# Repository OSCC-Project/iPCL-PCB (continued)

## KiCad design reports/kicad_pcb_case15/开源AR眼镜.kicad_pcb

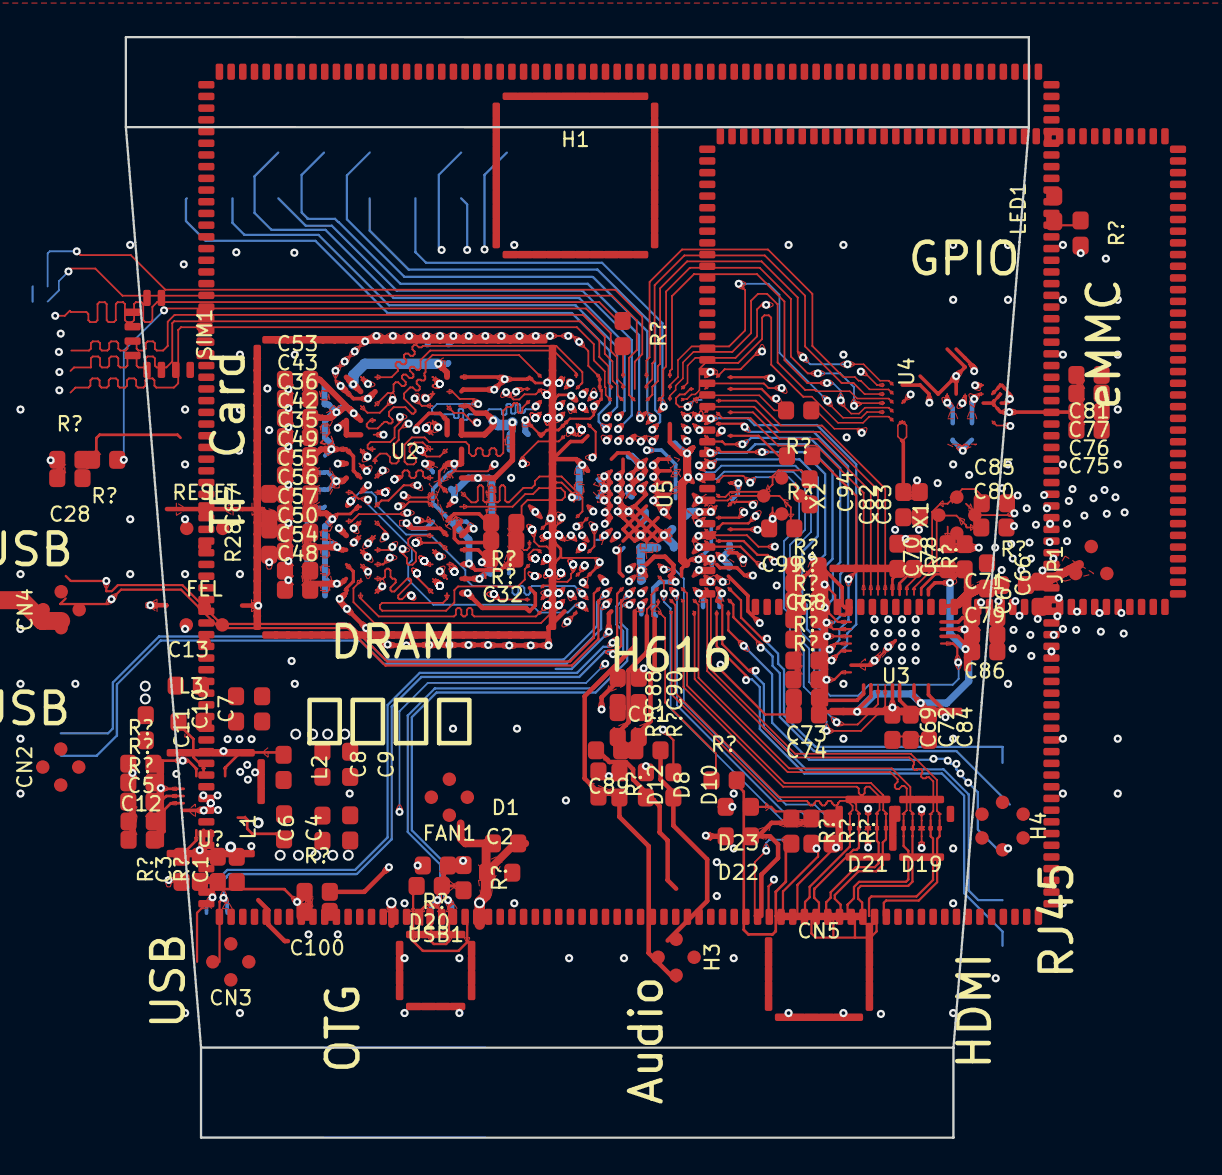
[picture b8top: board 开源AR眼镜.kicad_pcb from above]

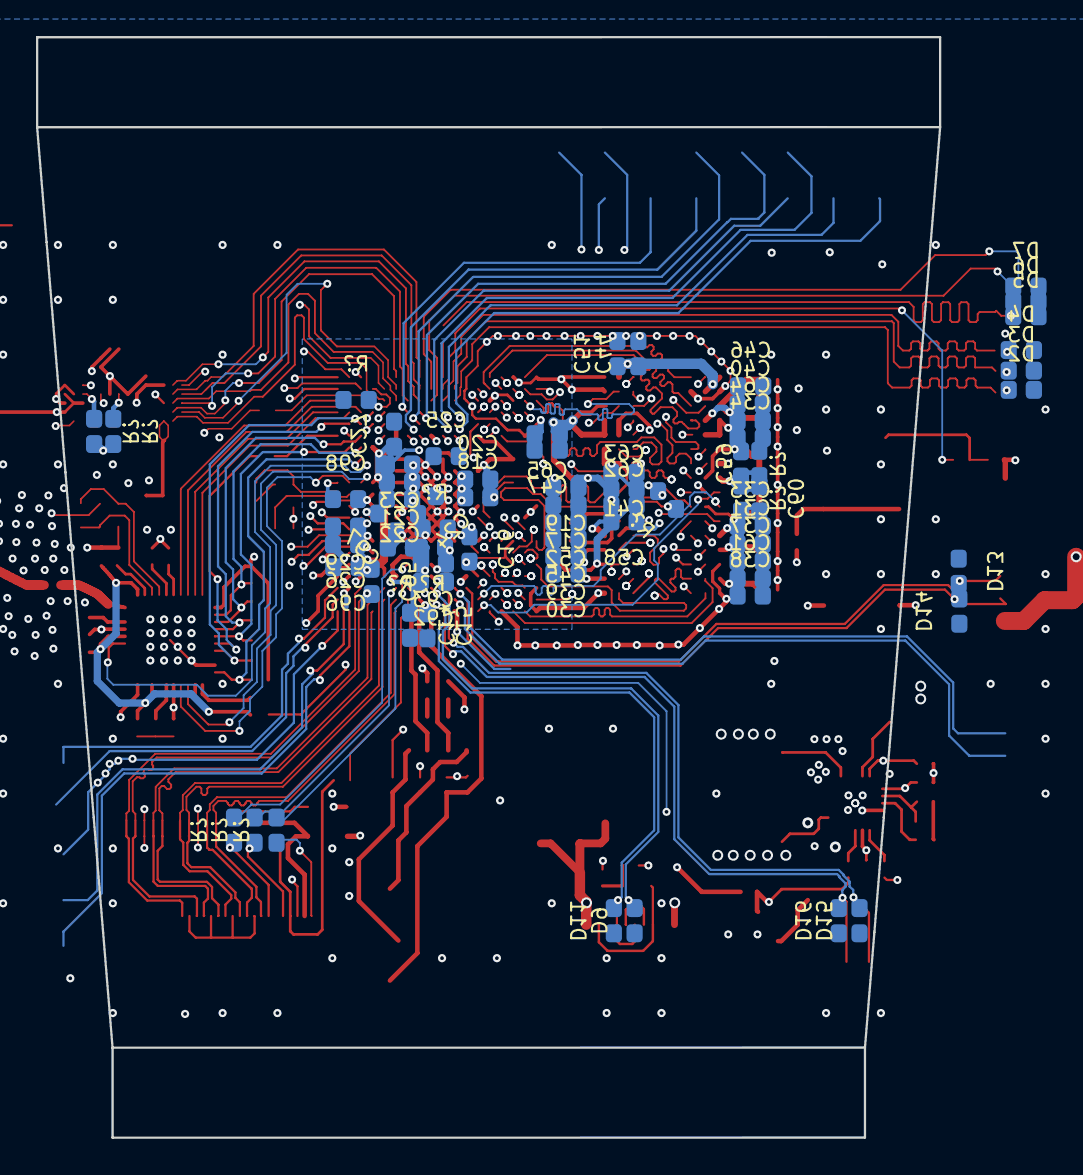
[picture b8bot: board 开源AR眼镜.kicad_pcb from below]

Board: 4 copper layers, 50.2 x 61.1 mm, 190 parts (68 on the bottom side), 205 nets.

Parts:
C1, C3, C5, C14, C15, C16, C17, C18, C19, C20, C21, C22, C23, C24, C25, C26, C27, C29, C30, C31, C32, C33, C34, C37, C38, C39, C40, C41, C44, C45, C46, C47, C51, C52, C58, C59, C60, C61, C62, C63, C64, C65, C68, C70, C80, C85, C87, C88, C89, C90, C91, C92, C93, C95, C96, C97, C98: 581fa90ba5d143178e8bfcf186ae1d70
C2, C4, C6, C7, C8, C9, C10, C11, C13: 7f9e4c2d894843118a1aeba95c797bcf
C12: e1052
C28: e10151
C35: e720
C36: e729
C42: e653
C43: e701
C48: e603
C49: e622
C50: e635
C53: e852
C54: e866
C55: e870
C56: e942
C57: e989
C66: e2714
C67: e2558
C69: e2711
C71: e2705
C72: e2696
C73: e2699
C74: e2684
C75: e2545
C76: e2548
C77: e2551
C78: e2687
C79: e2690
C81: e2555
C82: e2673
C83: e2681
C84: e2693
C86: 5623a01f87384e08a8b5290e5861d0f4
C94: e1
C99: e14
C100: e7893
CN2, CN3, CN4: 9f9cb2331b6a4c4f91b52175da028a24
CN5: 0ae1efe0f7d2407eb297bc7058fd8c69
D1, D22, D23: 2b17b6508c304f8397150a04154526c8
D2, D3, D4, D5, D6, D7, D9, D11, D13, D14, D15, D16: 0baea7e86dda406e868efb521e9c02e5
D8: e7662
D10: e7663
D12: e7664
D19, D21: d6df26df1b89462b9dbdd582f83a1450
D20: e1647
FAN1: 2922d851b26b41f2b163301ca83b4644
FEL: e7933
H1: e470
H3: 0876aa572ae04f9da46844e934f9581a
H4: ca1b601eea104326878baf7c393cc1b2
JP1: e807
L1, L2, L3: 19410787abb94090bd85a15924cf82ec
LED1: 94ee4ab7327a4e2984b11e8f42e0f02f
R28: 2e59de51ddd0459a8a47baced67eab54
R?: d8ec46ae5a094ccdab1991146694df6a
R?#2, R?#3, R?#4, R?#5, R?#6, R?#7, R?#8, R?#9, R?#10, R?#11, R?#12, R?#13, R?#14, R?#15, R?#16, R?#17, R?#18, R?#19, R?#20, R?#21, R?#22, R?#23, R?#24, R?#25, R?#26, R?#27, R?#28, R?#29, R?#30, R?#31, R?#32, R?#33, R?#34, R?#35, R?#36, R?#37, R?#38, R?#39, R?#40, R?#41, R?#42, R?#43, R?#44: d8ec46ae5a094ccdab1991146694df6a
RESET: e7925
SIM1: e708
U2: b0dac75ddcc0466e9dc68b643c109b9c
U3: f9eab8e05fad47a3923da328ceb5634b
U4: 492ce324e0ff4b6d98c834c55a53f5d1
U5: bf2799c56bdb4b9884a0d28b018f63fb
U?: ce05511545c44d0aa546a4655168694b
USB1: ced0c49f2f064bebbf04b9740ffb94f1
X1, X2: d871d424976d4e0f82d6b293e7e358f1

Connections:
1V8: C1.2, C14.2, C15.2, C16.2, C98.1, R?#18.1, R?#19.1, R?#32.2, U5.D11, U5.D12, U5.F18, U5.H17, U5.H20, U5.L14, U?.15
3V3: C3.2, C26.2, C27.2, C28.2, C29.2, C68.1, C69.1, C75.2, C76.2, C77.2, C81.2, C86.2, D23.2, H1.1, H1.17, R?.1, R?#2.1, R?#3.1, R?#4.1, R?#5.1, R?#6.1, R?#7.1, R?#8.1, R?#9.1, R?#10.1, R?#11.1, R?#27.2, R?#37.2, SIM1.4, U3.11, U3.25, U3.30, U3.37, U4.C6, U4.E6, U4.F5, U4.J10, U4.K9, U4.M4, U4.N4, U4.P3, U4.P5, U5.D7, U5.D10, U5.E18, U5.F5, U5.J6, U5.M18, U?.12
$1N16368: L1.1, U?.18
$1N16426: L2.1, U?.19
$1N16541: L3.1, U?.3
$1N24681: C5.2, R?#28.2, U?.7
$1N28880: R?#12.2, U?.11
$1N28962: R?#13.2, U?.13
$1N30789: C12.2, U?.8
$1N53902: LED1.1, R?#37.1
$2N2062: R?#42.1, U5.L15
$2N2223: R?#44.2, U2.L9
$2N2224: R?#43.2, U2.L8
$3N2117: C82.2, C83.2, U4.C2
$3N2831: R?#22.2, U5.D3
$3N3551: R?#3.2, R?#41.2, SIM1.11
$3N5546: C66.2, R?#14.1, U3.40
$3N5547: C67.2, JP1.1, R?#14.2
$3N5552: C73.1, U3.21
$3N5553: C70.1, U3.2
$3N5554: C71.1, U3.38
$3N5561: C72.1, U3.26
$3N5562: C74.1, C78.1, C79.1, C84.1, U3.1, U3.22, U3.28, U3.36
$3N5564: R?#6.2, U3.6
$3N5565: R?#2.2, U3.5
$3N9917: R?#21.2, U5.K1
$3N12389: R?#20.2, U5.A6
$3N73904: R?#33.1, U5.D2
$4N2198: C92.2, U5.J18
$4N2208: C93.2, U5.J17
$4N2209: R?#36.2, U5.K18
$4N2219: C95.2, U5.D18
$4N2220: C96.2, U5.C17
$4N2243: C97.1, U5.D13
$4N12583: D20.1, R?#27.1, R?#40.2
$4N26086: D23.1, R?#29.1
$4N34203: C91.2, D10.2, H3.2
$4N34315: C89.2, D8.2, H3.1
$4N36516: C88.2, R?#38.1
$4N36638: C90.2, R?#39.1
$4N42572: C87.1, R28.2, RESET.1, RESET.2
AGND: C92.1, C93.1, R?#15.2, R?#36.1, U5.H18
AP_REG_ON: U3.35, U5.C9
BT_RSTN: U3.23, U5.C10
D0+: D11.1, U5.J20, USB1.A6, USB1.B6
D0-: D9.1, U5.J19, USB1.A7, USB1.B7
D1+: CN4.3, D14.1, U5.M20
D1-: CN4.4, D13.1, U5.M19
D2+: CN2.3, U5.L20
D2-: CN2.4, U5.L19
D3+: CN3.3, D16.1, U5.K20
D3-: CN3.4, D15.1, U5.K19
EPHY_RXN: H4.6, U5.B21
EPHY_RXP: H4.5, U5.B20
EPHY_TXN: H4.3, U5.A20
EPHY_TXP: H4.2, U5.A19
FEL: FEL.1, FEL.2, U5.B17
GND: C1.1, C2.2, C3.1, C4.2, C5.1, C6.2, C7.2, C8.2, C9.2, C10.2, C11.2, C12.1, C13.2, C14.1, C15.1, C16.1, C17.1, C18.1, C19.1, C20.1, C21.1, C22.1, C23.1, C24.1, C25.1, C26.1, C27.1, C28.1, C29.1, C30.1, C31.1, C32.1, C33.1, C34.1, C35.1, C36.1, C37.1, C38.1, C39.1, C40.1, C41.1, C42.1, C43.1, C44.1, C45.1, C46.1, C47.1, C48.1, C49.1, C50.1, C51.1, C52.1, C53.1, C54.1, C55.1, C56.1, C57.1, C58.1, C59.1, C60.1, C61.1, C62.1, C63.1, C64.1, C65.1, C66.1, C67.1, C68.2, C69.2, C70.2, C71.2, C72.2, C73.2, C74.2, C75.1, C76.1, C77.1, C78.2, C79.2, C80.2, C81.1, C82.1, C83.1, C84.2, C85.2, C86.1, C87.2, C88.1, C90.1, C94.2, C95.1, C96.1, C97.2, C98.2, C99.2, C100.1, CN2.1, CN3.1, CN4.1, CN5.2, CN5.5, CN5.8, CN5.11, CN5.17, CN5.20, CN5.21, CN5.22, CN5.23, D2.1, D3.1, D4.1, D5.1, D6.1, D7.1, D8.1, D9.2, D10.1, D11.2, D12.1, D13.2, D14.2, D15.2, D16.2, D19.3, D19.8, D21.3, D21.8, FAN1.2, FAN1.3, FAN1.4, FEL.3, FEL.4, H1.6, H1.9, H1.14, H1.20, H1.25, H1.30, H1.34, H1.39, H3.4, H4.1, H4.4, JP1.2, JP1.3, LED1.2, R?#15.1, R?#17.1, R?#28.1, R?#33.2, R?#35.1, R?#42.2, R?#43.1, R?#44.1, RESET.3, RESET.4, SIM1.6, SIM1.9, SIM1.10, SIM1.12, SIM1.13, SIM1.14, U2.A9, U2.B1, U2.B3, U2.B9, U2.D1, U2.D8, U2.E1, U2.E2, U2.E8, U2.F9, U2.G1, U2.G8, U2.G9, U2.J2, U2.J8, U2.M1, U2.M9, U2.P1, U2.P9, U2.T1, U2.T9, U3.19, U3.41, U4.A6, U4.C4, U4.E7, U4.G5, U4.H10, U4.J5, U4.K8, U4.N2, U4.N5, U4.P4, U4.P6, U5.A1, U5.A10, U5.A18, U5.A21, U5.B6, U5.B16, U5.D19, U5.F14, U5.F15, U5.G13, U5.G14, U5.G15, U5.H10, U5.H11, U5.H12, U5.H13, U5.H14, U5.H15, U5.H19, U5.J12, U5.J13, U5.J14, U5.J15, U5.K8, U5.K9, U5.K10, U5.K11, U5.K12, U5.K13, U5.K14, U5.K15, U5.L21, U5.M1, U5.M2, U5.M3, U5.N6, U5.N9, U5.N12, U5.N15, U5.N18, U5.P3, U5.R5, U5.R21, U5.T1, U5.T3, U5.T8, U5.T10, U5.T15, U5.T17, U5.U6, U5.U13, U5.V1, U5.V5, U5.V12, U5.V19, U5.V21, U?.9, U?.21, USB1.12, USB1.13, USB1.14, USB1.15, USB1.A1B12, USB1.B1A12, X1.2, X1.4, X2.2, X2.4
H5V: CN5.18, D22.1, R?#30.1, R?#31.1
HCEC: R?#24.1, U5.G17
HDCEC: CN5.13, R?#24.2, R?#29.2
HDHPD: CN5.19, R?#34.2
HDMI_0N: CN5.9, D21.2, D21.9, U5.E20
HDMI_0P: CN5.7, D21.1, D21.10, U5.E19
HDMI_1N: CN5.6, D19.5, D19.6, U5.D21
HDMI_1P: CN5.4, D19.4, D19.7, U5.D20
HDMI_2N: CN5.3, D19.2, D19.9, U5.C20
HDMI_2P: CN5.1, D19.1, D19.10, U5.C19
HDMI_CN: CN5.12, D21.5, D21.6, U5.F21
HDMI_CP: CN5.10, D21.4, D21.7, U5.F20
HDSCL: CN5.15, R?#25.2, R?#30.2
HDSDA: CN5.16, R?#26.2, R?#31.2
HHPD: R?#34.1, U5.G18
HSCL: R?#25.1, U5.F19
HSDA: R?#26.1, U5.G21
HXIN: C94.1, U5.B11, X2.1
HXOUT: C99.1, U5.C12, X2.3
IRQ: R?#12.1, U5.C1
LL: C89.1, R?#38.2, U5.G19
LPCLK: R?#5.2, U3.20, U5.C8
LR: C91.1, R?#39.2, U5.G20
PH0: H1.23, U5.D16
PH1: H1.22, U5.D15
PH2: H1.37, U5.B15
PH3: H1.40, U5.C15
PH4: H1.35, U5.A14
PH5: H1.27, U5.B14
PH6: H1.38, U5.C14
PH7: H1.24, U5.B12
PH8: H1.21, U5.C13
PH9: H1.28, U5.A12
PH10: H1.26, U5.B13
PI0: H1.18, U5.H6
PI1: H1.32, U5.D4
PI2: H1.19, U5.G6
PI3: H1.29, U5.E4
PI4: H1.11, U5.G5
PI5: H1.10, U5.H4
PI6: H1.12, U5.H5
PI7: H1.13, U5.G4
PI8: H1.36, U5.E6
PI9: H1.31, U5.D5
PI10: H1.3, U5.L5
PI11: H1.8, U5.K4
PI12: H1.7, U5.K5
PI13: H1.33, U5.E5
PI14: H1.16, U5.L6
PI15: H1.5, U5.L4
PI16: H1.15, U5.K6
PMU_SCK: R?#19.2, U5.C18, U?.6
PMU_SDA: R?#18.2, U5.B18, U?.5
PS: C2.1, C7.1, C10.1, CN2.2, CN3.2, CN4.2, D1.1, D1.2, D22.2, FAN1.1, H1.2, H1.4, U?.2, U?.17, U?.20, USB1.A4B9, USB1.B4A9
RESET: C100.2, R28.1, R?#13.1, R?#32.1, U5.A16
SA0: U2.N3, U5.P18
SA1: U2.P7, U5.R15
SA2: U2.P3, U5.T18
SA3: U2.N2, U5.R19
SA4: U2.P8, U5.U16
SA5: U2.P2, U5.R20
SA6: U2.R8, U5.N13
SA7: U2.R2, U5.T21
SA8: U2.T8, U5.V17
SA9: U2.R3, U5.T20
SA10: U2.L7, U5.U19
SA11: U2.R7, U5.U17
SA12: U2.N7, U5.P16
SA13: U2.T3, U5.R18
SA14: U2.T7, U5.P15
SA15: U2.M7, U5.U18
SBA0: U2.M2, U5.P20
SBA1: U2.N8, U5.U15
SBA2: U2.M3, U5.U20
SCAS: U2.K3, U5.N16
SCKE0: U2.K9, U5.V15
SCKE1: U2.J9, U5.P13
SCKN: R?#23.2, U2.K7, U5.U14
SCKP: R?#23.1, U2.J7, U5.T14
SCS0: U2.L2, U5.P21
SCS1: U2.L1, U5.N19
SDC0_CLK: D5.2, R?#21.1, SIM1.5
SDC0_CMD: D4.2, SIM1.3, U5.K3
SDC0_D0: D6.2, SIM1.7, U5.J3
SDC0_D1: D7.2, SIM1.8, U5.J2
SDC0_D2: D2.2, SIM1.1, U5.L3
SDC0_D3: D3.2, SIM1.2, U5.L2
SDC0_DET: R?#41.1, U5.K2
SDC1_CLK: R?#20.1, U3.16
SDC1_CMD: R?.2, U3.12, U5.C7
SDC1_D0: R?#7.2, U3.13, U5.C6
SDC1_D1: R?#8.2, U3.14, U5.B5
SDC1_D2: R?#9.2, U3.17, U5.C5
SDC1_D3: R?#4.2, U3.15, U5.B7
SDC2_CLK: R?#22.1, U4.M6
SDC2_CMD: R?#10.2, U4.M5, U5.E2
SDC2_D0: U4.A3, U5.F2
SDC2_D1: U4.A4, U5.G3
SDC2_D2: U4.A5, U5.H2
SDC2_D3: U4.B2, U5.E3
SDC2_D4: U4.B3, U5.F1
SDC2_D5: U4.B4, U5.F3
SDC2_D6: U4.B5, U5.H1
SDC2_D7: U4.B6, U5.H3
SDC2_DS: R?#11.2, U4.H5, U5.B1
SDC2_RST: U4.K5, U5.C2
SDQ0: U2.A2, U5.N3
SDQ1: U2.C8, U5.U4
SDQ2: U2.C2, U5.N2
SDQ3: U2.D7, U5.T4
SDQ4: U2.B8, U5.U3
SDQ5: U2.C3, U5.P1
SDQ6: U2.A7, U5.T2
SDQ7: U2.A3, U5.P2
SDQ8: U2.G2, U5.P5
SDQ9: U2.F7, U5.V3
SDQ10: U2.F2, U5.P4
SDQ11: U2.E3, U5.R4
SDQ12: U2.H8, U5.R6
SDQ13: U2.H3, U5.N4
SDQ14: U2.F8, U5.P6
SDQ15: U2.H7, U5.N5
SDQM0: U2.D3, U5.U1
SDQM1: U2.E7, U5.R3
SDQS0N: U2.B7, U5.R1
SDQS0P: U2.C7, U5.R2
SDQS1N: U2.G3, U5.V2
SDQS1P: U2.F3, U5.U2
SODT0: U2.K1, U5.N20
SODT1: U2.J1, U5.N21
SRAS: U2.J3, U5.T16
SRST: U2.T2, U5.U21
SVREF: C58.2, C59.2, C60.2, R?#16.1, R?#17.2, U2.H1, U2.M8
SWE: U2.L3, U5.V20
TV_OUT: D12.2, H3.3, R?#35.2, U5.J21
UART1_CTS: U3.7, U5.B3
UART1_RTS: U3.8, U5.C4
UART1_RX: U3.10, U5.B4
UART1_TX: U3.9, U5.A4
USB0_ID: D20.2, USB1.A5, USB1.B5
USB_ID: R?#40.1, U5.A2
VCC_DRAM: C11.1, C13.1, C17.2, C18.2, C19.2, C20.2, C30.2, C31.2, C32.2, C33.2, C34.2, C35.2, C36.2, C37.2, C38.2, C39.2, C40.2, C41.2, C42.2, C43.2, C44.2, C45.2, C46.2, C47.2, C48.2, C49.2, C50.2, C51.2, C52.2, C53.2, C54.2, C55.2, C56.2, C57.2, C61.2, C62.2, C63.2, C64.2, C65.2, L3.2, R?#16.2, U2.A1, U2.A8, U2.B2, U2.C1, U2.C9, U2.D2, U2.D9, U2.E9, U2.F1, U2.G7, U2.H2, U2.H9, U2.K2, U2.K8, U2.N1, U2.N9, U2.R1, U2.R9, U5.L9, U5.L10, U5.L11, U5.L12, U5.L13, U?.4
VDD_CPU: C8.1, C9.1, C24.2, C25.2, L2.2, U5.H8, U5.H9, U5.J8, U5.J9, U5.J10, U5.J11, U5.L8, U?.1
VDD_GPU: C4.1, C6.1, C21.2, C22.2, C23.2, L1.2, U5.F8, U5.F9, U5.F10, U5.F11, U5.F12, U5.F13, U5.G8, U5.G9, U5.G10, U5.G11, U5.G12, U?.16
WHXI: C80.1, U3.3, X1.1
WHXO: C85.1, U3.4, X1.3
WL_REG_ON: U3.24, U5.B10

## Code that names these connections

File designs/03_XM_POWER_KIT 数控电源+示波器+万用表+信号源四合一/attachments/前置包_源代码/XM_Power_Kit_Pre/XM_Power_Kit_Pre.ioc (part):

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Mcu.Name=STM32F407V(E-G)Tx
Mcu.Package=LQFP100
Mcu.UserName=STM32F407VETx
PA10.GPIOParameters=GPIO_Label
PA10.GPIO_Label=FAN_PWM_T1C3
PA10.Signal=S_TIM1_CH3
PA11.Mode=Device_Only
PA11.Signal=USB_OTG_FS_DM
PA12.Mode=Device_Only
PA12.Signal=USB_OTG_FS_DP
PA13.Mode=Serial_Wire
PA13.Signal=SYS_JTMS-SWDIO
PA14.Mode=Serial_Wire
PA14.Signal=SYS_JTCK-SWCLK
PA15.GPIOParameters=GPIO_Label
PA15.GPIO_Label=SWITCH_I
PA15.Signal=GPIO_Output
PA3.Signal=ADCx_IN3
PA4.Signal=COMP_DAC1_group
PA5.Signal=COMP_DAC2_group
PA8.Mode=I2C
PA8.Signal=I2C3_SCL
PA9.GPIOParameters=GPIO_Label
PA9.GPIO_Label=LCD_PWM_T1C2
PA9.Signal=S_TIM1_CH2
PB10.Mode=Asynchronous
PB10.Signal=USART3_TX
PB11.Mode=Asynchronous
PB11.Signal=USART3_RX
PB12.GPIOParameters=GPIO_Label
PB12.GPIO_Label=KEY_MODE
PB12.Signal=GPIO_Input
PB13.GPIOParameters=GPIO_Label
PB13.GPIO_Label=KEY_UP
PB13.Signal=GPIO_Input
PB14.GPIOParameters=GPIO_Label
PB14.GPIO_Label=KEY_DOWN
PB14.Signal=GPIO_Input
PB15.GPIOParameters=GPIO_Label
PB15.GPIO_Label=KEY_SET
PB15.Signal=GPIO_Input
PB3.GPIOParameters=GPIO_Label
PB3.GPIO_Label=FLASH_SPI1_SCK
PB3.Mode=Full_Duplex_Master
PB3.Signal=SPI1_SCK
PB4.GPIOParameters=GPIO_Label
PB4.GPIO_Label=FLASH_SPI1_MISO
PB4.Mode=Full_Duplex_Master
PB4.Signal=SPI1_MISO
PB5.GPIOParameters=GPIO_Label
PB5.GPIO_Label=FLASH_SPI1_MOSI
PB5.Mode=Full_Duplex_Master
PB5.Signal=SPI1_MOSI
PB6.Mode=I2C
PB6.Signal=I2C1_SCL
PB7.Mode=I2C
PB7.Signal=I2C1_SDA
PC0.GPIOParameters=PinState,GPIO_Label
PC0.GPIO_Label=SYS_LED
PC0.PinState=GPIO_PIN_SET
PC0.Signal=GPIO_Output
PC1.GPIOParameters=GPIO_Label
PC1.GPIO_Label=AT1/5
PC1.Signal=GPIO_Output
PC10.GPIOParameters=GPIO_Label
PC10.GPIO_Label=DC_SWITCH_GND
PC10.Signal=GPIO_Output
PC11.GPIOParameters=PinState,GPIO_Label
PC11.GPIO_Label=SWITCH_DC
PC11.PinState=GPIO_PIN_SET
PC11.Signal=GPIO_Output
PC12.GPIOParameters=GPIO_Label
PC12.GPIO_Label=SWITCH_V
PC12.Signal=GPIO_Output
PC13-ANTI_TAMP.GPIOParameters=PinState,GPIO_Label
PC13-ANTI_TAMP.GPIO_Label=S2
PC13-ANTI_TAMP.PinState=GPIO_PIN_SET
PC13-ANTI_TAMP.Signal=GPIO_Output
PC14-OSC32_IN.GPIOParameters=GPIO_Label
PC14-OSC32_IN.GPIO_Label=S1
PC14-OSC32_IN.Signal=GPIO_Output
PC15-OSC32_OUT.GPIOParameters=GPIO_Label
PC15-OSC32_OUT.GPIO_Label=S0
PC15-OSC32_OUT.Signal=GPIO_Output
PC2.GPIOParameters=PinState,GPIO_Label
PC2.GPIO_Label=DC/AC
PC2.PinState=GPIO_PIN_SET
PC2.Signal=GPIO_Output
PC3.GPIOParameters=GPIO_Label
PC3.GPIO_Label=LCD_RST
PC3.Signal=GPIO_Output
PC6.GPIOParameters=GPIO_Label
PC6.GPIO_Label=ECD_S
PC6.Signal=GPIO_Input
PC7.GPIOParameters=GPIO_Label
PC7.GPIO_Label=DMM_SWITCH_GND
PC7.Signal=GPIO_Output
PC8.Signal=S_TIM3_CH3
PC9.Mode=I2C
PC9.Signal=I2C3_SDA
PD0.Mode=16b-d1
PD0.Signal=FSMC_D2
PD1.Mode=16b-d1
PD1.Signal=FSMC_D3
PD10.Mode=16b-d1
PD10.Signal=FSMC_D15
PD11.Mode=A16_1
PD11.Signal=FSMC_A16
PD12.GPIOParameters=GPIO_Label
PD12.GPIO_Label=ECD_B
PD12.Signal=S_TIM4_CH1
PD13.GPIOParameters=GPIO_Label
PD13.GPIO_Label=ECD_A
PD13.Signal=S_TIM4_CH2
PD14.Mode=16b-d1
PD14.Signal=FSMC_D0
PD15.Mode=16b-d1
PD15.Signal=FSMC_D1
PD2.GPIOParameters=GPIO_Label
PD2.GPIO_Label=P_EN
PD2.Signal=GPIO_Output
PD3.GPIOParameters=GPIO_Label
PD3.GPIO_Label=SW_RELEASE
PD3.Signal=GPIO_Output
PD4.Mode=Lcd1
PD4.Signal=FSMC_NOE
PD5.Mode=Lcd1
PD5.Signal=FSMC_NWE
PD6.GPIOParameters=PinState,GPIO_Label
PD6.GPIO_Label=FLASH_CS
PD6.PinState=GPIO_PIN_SET
PD6.Signal=GPIO_Output
PD7.Mode=NorPsramChipSelect1_1
PD7.Signal=FSMC_NE1
PD8.Mode=16b-d1
PD8.Signal=FSMC_D13
PD9.Mode=16b-d1
PD9.Signal=FSMC_D14
PE0.GPIOParameters=GPIO_Label
PE0.GPIO_Label=SWITCH_R/C
PE0.Signal=GPIO_Output
PE1.GPIOParameters=PinState,GPIO_Label
PE1.GPIO_Label=SW_200
PE1.PinState=GPIO_PIN_SET
PE1.Signal=GPIO_Output
PE10.Mode=16b-d1
PE10.Signal=FSMC_D7
PE11.Mode=16b-d1
PE11.Signal=FSMC_D8
PE12.Mode=16b-d1
PE12.Signal=FSMC_D9
PE13.Mode=16b-d1
PE13.Signal=FSMC_D10
PE14.Mode=16b-d1
PE14.Signal=FSMC_D11
PE15.Mode=16b-d1
PE15.Signal=FSMC_D12
PE2.GPIOParameters=PinState,GPIO_Label
PE2.GPIO_Label=SW_10K
PE2.PinState=GPIO_PIN_SET
PE2.Signal=GPIO_Output
PE3.GPIOParameters=PinState,GPIO_Label
PE3.GPIO_Label=SW_100K
PE3.PinState=GPIO_PIN_SET
PE3.Signal=GPIO_Output
PE4.GPIOParameters=GPIO_Label
PE4.GPIO_Label=KEY_PWR_ON/OFF
PE4.Signal=GPIO_Input
PE5.GPIOParameters=GPIO_Label
PE5.GPIO_Label=BEEZER
PE5.Signal=S_TIM9_CH1
PE7.Mode=16b-d1
PE7.Signal=FSMC_D4
PE8.Mode=16b-d1
PE8.Signal=FSMC_D5
PE9.Mode=16b-d1
PE9.Signal=FSMC_D6
PH0-OSC_IN.Mode=HSE-External-Oscillator
PH0-OSC_IN.Signal=RCC_OSC_IN
PH1-OSC_OUT.Mode=HSE-External-Oscillator
PH1-OSC_OUT.Signal=RCC_OSC_OUT
RCC.HSE_VALUE=8000000
RCC.SYSCLKFreq_VALUE=144000000
RCC.SYSCLKSource=RCC_SYSCLKSOURCE_PLLCLK
board=custom

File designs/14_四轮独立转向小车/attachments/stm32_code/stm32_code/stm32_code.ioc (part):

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Mcu.Name=STM32F407V(E-G)Tx
Mcu.Package=LQFP100
Mcu.UserName=STM32F407VETx
PA0-WKUP.GPIOParameters=GPIO_Label
PA0-WKUP.GPIO_Label=M3A
PA0-WKUP.Signal=S_TIM5_CH1
PA1.GPIOParameters=GPIO_Label
PA1.GPIO_Label=M3B
PA1.Signal=S_TIM5_CH2
PA10.Mode=Asynchronous
PA10.Signal=USART1_RX
PA13.Mode=Serial_Wire
PA13.Signal=SYS_JTMS-SWDIO
PA14.Mode=Serial_Wire
PA14.Signal=SYS_JTCK-SWCLK
PA15.GPIOParameters=GPIO_ModeDefaultPP,GPIO_Label
PA15.GPIO_Label=D1
PA15.GPIO_ModeDefaultPP=GPIO_MODE_AF_OD
PA15.Signal=S_TIM2_CH1_ETR
PA2.GPIOParameters=GPIO_Label
PA2.GPIO_Label=M4A
PA2.Signal=S_TIM5_CH3
PA3.GPIOParameters=GPIO_Label
PA3.GPIO_Label=M4B
PA3.Signal=S_TIM5_CH4
PA5.Mode=Full_Duplex_Master
PA5.Signal=SPI1_SCK
PA6.GPIOParameters=GPIO_Label
PA6.GPIO_Label=B2A
PA6.Signal=S_TIM3_CH1
PA7.GPIOParameters=GPIO_Label
PA7.GPIO_Label=B2B
PA7.Signal=S_TIM3_CH2
PA8.Mode=I2C
PA8.Signal=I2C3_SCL
PA9.Mode=Asynchronous
PA9.Signal=USART1_TX
PB10.GPIOParameters=GPIO_ModeDefaultPP,GPIO_Label
PB10.GPIO_Label=D3
PB10.GPIO_ModeDefaultPP=GPIO_MODE_AF_OD
PB10.Signal=S_TIM2_CH3
PB11.GPIOParameters=GPIO_ModeDefaultPP,GPIO_Label
PB11.GPIO_Label=D4
PB11.GPIO_ModeDefaultPP=GPIO_MODE_AF_OD
PB11.Signal=S_TIM2_CH4
PB12.GPIOParameters=GPIO_PuPd,GPIO_Label
PB12.GPIO_Label=CS2
PB12.GPIO_PuPd=GPIO_PULLUP
PB12.Signal=GPIO_Output
PB13.GPIOParameters=GPIO_PuPd,GPIO_Label
PB13.GPIO_Label=CS1
PB13.GPIO_PuPd=GPIO_PULLUP
PB13.Signal=GPIO_Output
PB14.GPIOParameters=GPIO_Label
PB14.GPIO_Label=M1A
PB14.Signal=S_TIM12_CH1
PB15.GPIOParameters=GPIO_Label
PB15.GPIO_Label=M1B
PB15.Signal=S_TIM12_CH2
PB3.GPIOParameters=GPIO_ModeDefaultPP,GPIO_Label
PB3.GPIO_Label=D2
PB3.GPIO_ModeDefaultPP=GPIO_MODE_AF_OD
PB3.Signal=S_TIM2_CH2
PB4.Mode=Full_Duplex_Master
PB4.Signal=SPI1_MISO
PB5.Mode=Full_Duplex_Master
PB5.Signal=SPI1_MOSI
PB6.GPIOParameters=GPIO_Label
PB6.GPIO_Label=NRF_CSN
PB6.Signal=GPIO_Output
PB7.GPIOParameters=GPIO_Label
PB7.GPIO_Label=NRF_CE
PB7.Signal=GPIO_Output
PC14-OSC32_IN.Mode=LSE-External-Oscillator
PC14-OSC32_IN.Signal=RCC_OSC32_IN
PC15-OSC32_OUT.Mode=LSE-External-Oscillator
PC15-OSC32_OUT.Signal=RCC_OSC32_OUT
PC6.GPIOParameters=GPIO_Label
PC6.GPIO_Label=B4A
PC6.Signal=S_TIM8_CH1
PC7.GPIOParameters=GPIO_Label
PC7.GPIO_Label=B4B
PC7.Signal=S_TIM8_CH2
PC9.Mode=I2C
PC9.Signal=I2C3_SDA
PD12.GPIOParameters=GPIO_Label
PD12.GPIO_Label=B3A
PD12.Signal=S_TIM4_CH1
PD13.GPIOParameters=GPIO_Label
PD13.GPIO_Label=B3B
PD13.Signal=S_TIM4_CH2
PD3.GPIOParameters=GPIO_PuPd,GPIO_Label
PD3.GPIO_Label=NRF_IQR
PD3.GPIO_PuPd=GPIO_PULLUP
PD3.Signal=GPIO_Input
PD5.Mode=Asynchronous
PD5.Signal=USART2_TX
PD6.Mode=Asynchronous
PD6.Signal=USART2_RX
PD8.GPIOParameters=GPIO_Label
PD8.GPIO_Label=IMU_TEST
PD8.Signal=GPIO_Output
PD9.GPIOParameters=GPIO_Label
PD9.GPIO_Label=BUZZ
PD9.Signal=GPIO_Output
PE11.GPIOParameters=GPIO_Label
PE11.GPIO_Label=B1B
PE11.Signal=S_TIM1_CH2
PE5.GPIOParameters=GPIO_Label
PE5.GPIO_Label=M2A
PE5.Signal=S_TIM9_CH1
PE6.GPIOParameters=GPIO_Label
PE6.GPIO_Label=M2B
PE6.Signal=S_TIM9_CH2
PE9.GPIOParameters=GPIO_Label
PE9.GPIO_Label=B1A
PE9.Signal=S_TIM1_CH1
PH0-OSC_IN.Mode=HSE-External-Oscillator
PH0-OSC_IN.Signal=RCC_OSC_IN
PH1-OSC_OUT.Mode=HSE-External-Oscillator
PH1-OSC_OUT.Signal=RCC_OSC_OUT
RCC.HSE_VALUE=8000000
RCC.SYSCLKFreq_VALUE=84000000
RCC.SYSCLKSource=RCC_SYSCLKSOURCE_PLLCLK
board=custom
